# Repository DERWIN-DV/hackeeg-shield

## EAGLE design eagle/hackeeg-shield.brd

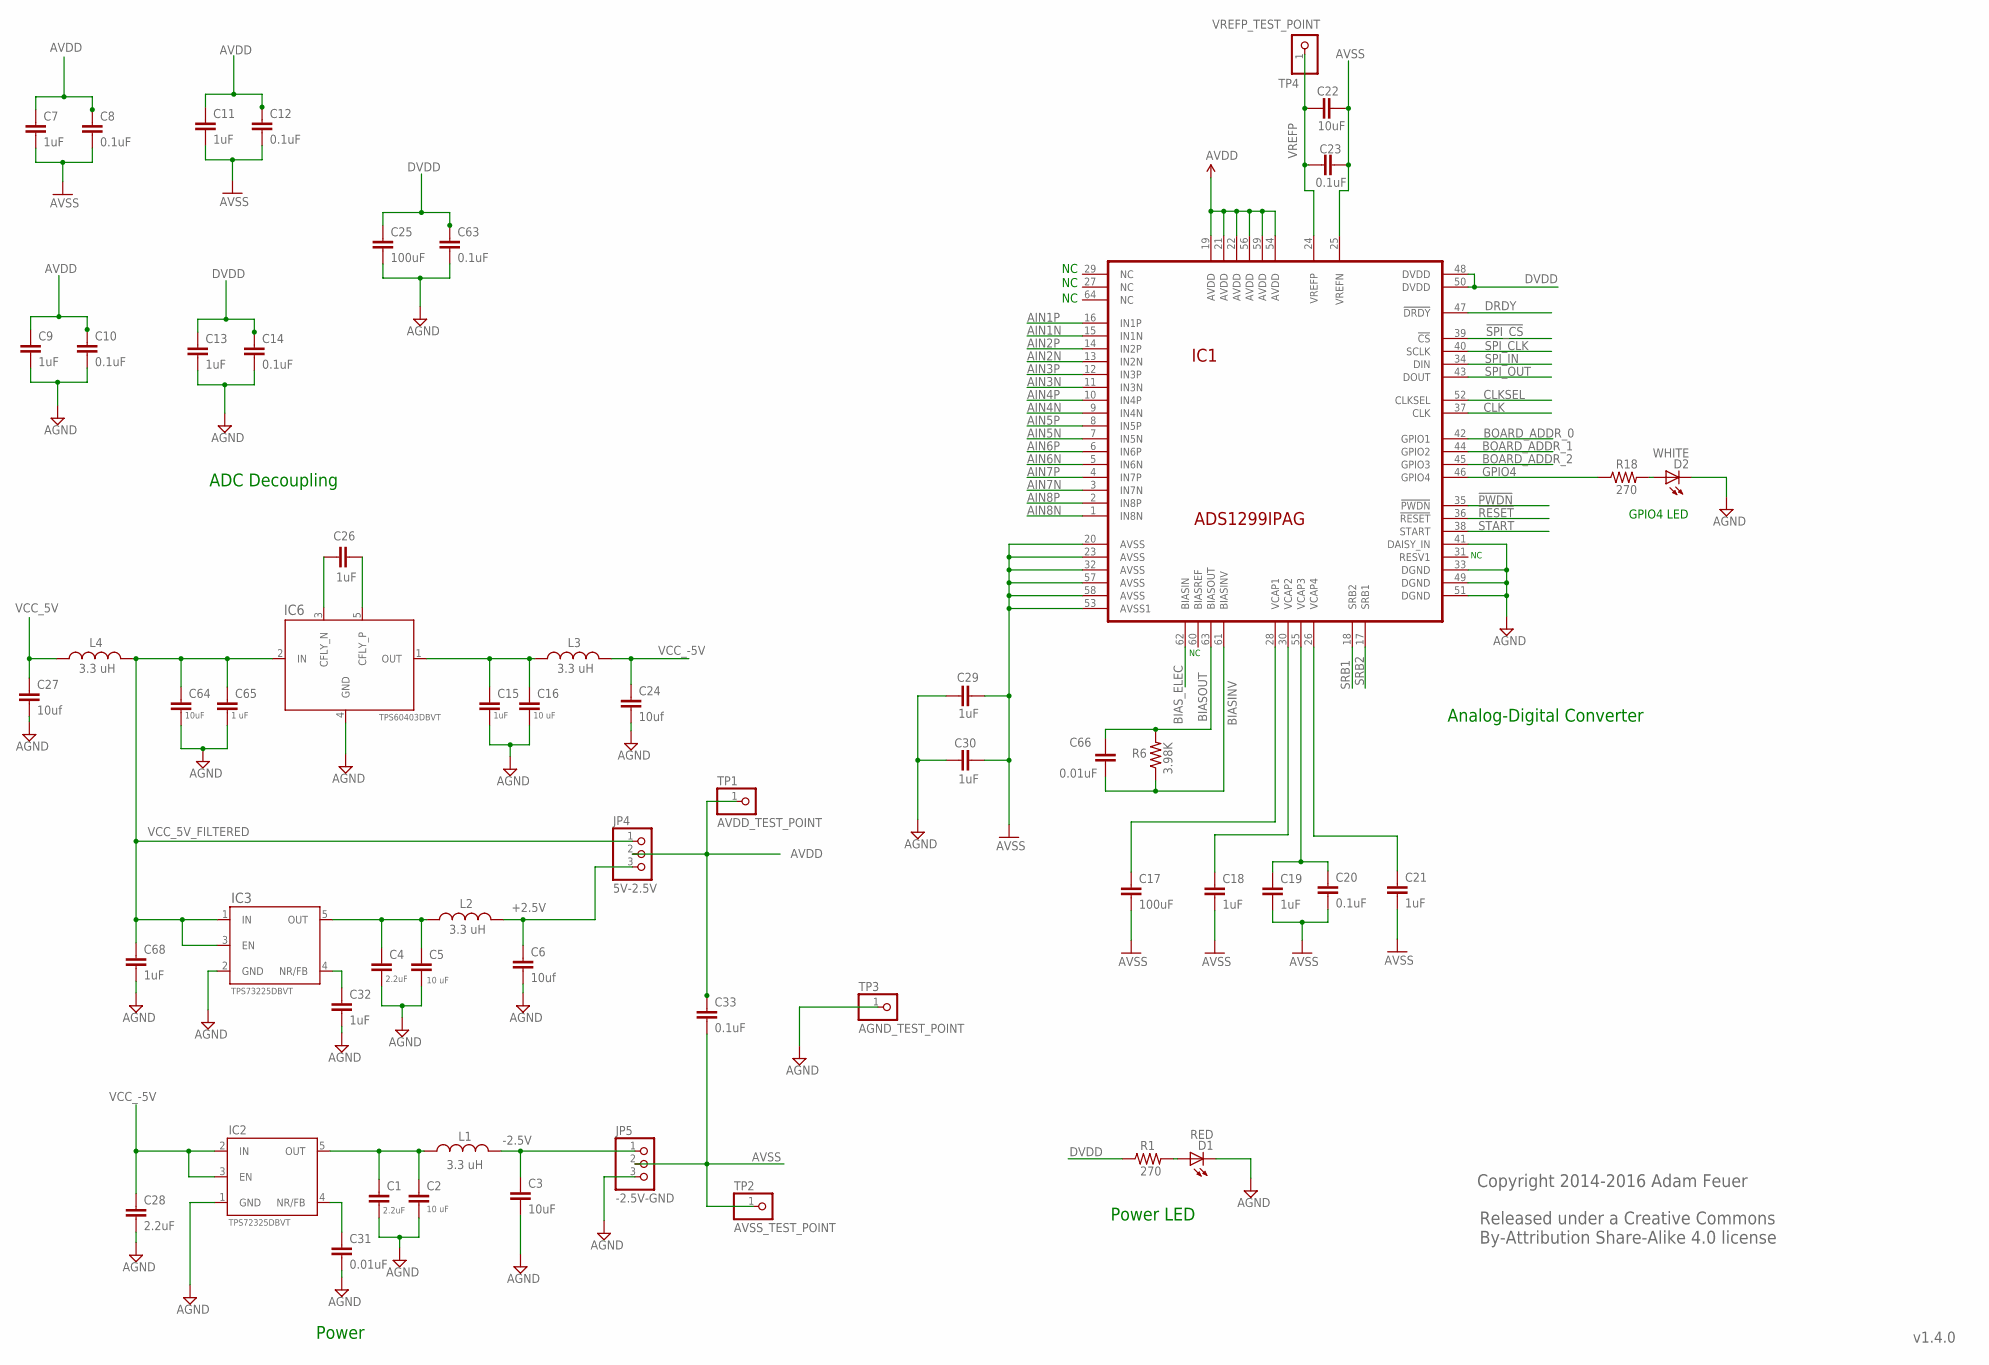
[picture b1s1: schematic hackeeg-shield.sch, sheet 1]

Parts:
C1, C4, C28: 2.2uF; 0603-CAP
C2, C5, C16: 10 uF; 0603-CAP
C3, C22, C64: 10uF; 0603-CAP
C6, C24, C27: 10uf; 0603-CAP
C7, C9, C11, C13, C15, C18, C19, C21, C26, C29, C30, C32, C68: 1uF; 0603-CAP
C8, C10, C12, C14, C20, C23, C33, C63: 0.1uF; 0603-CAP
C17, C25: 100uF; 1210
C31, C66: 0.01uF; 0603-CAP
C65: 1 uF; 0603-CAP
D1: RED; LED-1206
D2: WHITE; LED-1206
IC1: ADS1299IPAG; TQFP64
IC2: TPS72325DBVT; SOT23-5
IC3: TPS73225DBVT; SOT23-5
IC6: TPS60403DBVT; SOT23-5
JP4: 5V-2.5V; 1X03
JP5: -2.5V-GND; 1X03
L1, L2, L3, L4: 3.3 uH; 0805
R1, R18: 270; 0603-RES
R6: 3.98K; 0603-RES
TP1: AVDD_TEST_POINT; 1X01
TP2: AVSS_TEST_POINT; 1X01
TP3: AGND_TEST_POINT; 1X01
TP4: VREFP_TEST_POINT; 1X01

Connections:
!PWDN: IC1.35 (!PWDN); also elsewhere on the board
!RESET: IC1.36 (!RESET); also elsewhere on the board
!SPI_CS: IC1.39 (!CS); also elsewhere on the board
+2.5V: C6.1, JP4.3, L2.2
-2.5V: C3.1, JP5.1, L1.2
AGND: C1.2, C2.2, C3.2, C4.2, C5.2, C6.2, C9.2, C10.2, C13.2, C14.2, C15.2, C16.2, C24.2, C25.2, C27.2, C28.2, C29.1, C30.1, C31.2, C32.2, C63.2, C64.2, C65.2, C68.2, D1.C, D2.C, IC1.33 (DGND), IC1.41 (DAISY_IN), IC1.49 (DGND), IC1.51 (DGND), IC2.1 (GND), IC3.2 (GND), IC6.4 (GND), JP5.3, TP3.1; also elsewhere on the board
AIN1N: IC1.15 (IN1N); also elsewhere on the board
AIN1P: IC1.16 (IN1P); also elsewhere on the board
AIN2N: IC1.13 (IN2N); also elsewhere on the board
AIN2P: IC1.14 (IN2P); also elsewhere on the board
AIN3N: IC1.11 (IN3N); also elsewhere on the board
AIN3P: IC1.12 (IN3P); also elsewhere on the board
AIN4N: IC1.9 (IN4N); also elsewhere on the board
AIN4P: IC1.10 (IN4P); also elsewhere on the board
AIN5N: IC1.7 (IN5N); also elsewhere on the board
AIN5P: IC1.8 (IN5P); also elsewhere on the board
AIN6N: IC1.5 (IN6N); also elsewhere on the board
AIN6P: IC1.6 (IN6P); also elsewhere on the board
AIN7N: IC1.3 (IN7N); also elsewhere on the board
AIN7P: IC1.4 (IN7P); also elsewhere on the board
AIN8N: IC1.1 (IN8N); also elsewhere on the board
AIN8P: IC1.2 (IN8P); also elsewhere on the board
AVDD: C7.1, C8.1, C9.1, C10.1, C11.1, C12.1, C33.1, IC1.19 (AVDD), IC1.21 (AVDD), IC1.22 (AVDD), IC1.54 (AVDD), IC1.56 (AVDD), IC1.59 (AVDD), JP4.2, TP1.1; also elsewhere on the board
AVSS: C7.2, C8.2, C11.2, C12.2, C17.2, C18.2, C19.2, C20.2, C21.2, C22.2, C23.2, C29.2, C30.2, C33.2, IC1.20 (AVSS), IC1.23 (AVSS), IC1.25 (VREFN), IC1.32 (AVSS), IC1.53 (AVSS1), IC1.57 (AVSS), IC1.58 (AVSS), JP5.2, TP2.1; also elsewhere on the board
BIASINV: C66.2, IC1.61 (BIASINV), R6.1; also elsewhere on the board
BIASOUT: C66.1, IC1.63 (BIASOUT), R6.2; also elsewhere on the board
BIAS_ELEC: IC1.62 (BIASIN); also elsewhere on the board
BOARD_ADDR_0: IC1.42 (GPIO1); also elsewhere on the board
BOARD_ADDR_1: IC1.44 (GPIO2); also elsewhere on the board
BOARD_ADDR_2: IC1.45 (GPIO3); also elsewhere on the board
CLK: IC1.37 (CLK); also elsewhere on the board
CLKSEL: IC1.52 (CLKSEL); also elsewhere on the board
DRDY: IC1.47 (!DRDY); also elsewhere on the board
DVDD: C13.1, C14.1, C25.1, C63.1, IC1.48 (DVDD), IC1.50 (DVDD), R1.1; also elsewhere on the board
GPIO4: IC1.46 (GPIO4), R18.1
unnamed: C4.1, C5.1, IC3.5 (OUT), L2.1
unnamed: C1.1, C2.1, IC2.5 (OUT), L1.1
unnamed: C17.1, IC1.28 (VCAP1)
unnamed: C18.1, IC1.30 (VCAP2)
unnamed: C19.1, C20.1, IC1.55 (VCAP3)
unnamed: C15.1, C16.1, IC6.1 (OUT), L3.1
unnamed: C21.1, IC1.26 (VCAP4)
unnamed: C26.2, IC6.5 (CFLY_P)
unnamed: C26.1, IC6.3 (CFLY_N)
unnamed: C32.1, IC3.4 (NR/FB)
unnamed: C31.1, IC2.4 (NR/FB)
unnamed: D2.A, R18.2
unnamed: D1.A, R1.2
SPI_CLK: IC1.40 (SCLK); also elsewhere on the board
SPI_IN: IC1.34 (DIN); also elsewhere on the board
SPI_OUT: IC1.43 (DOUT); also elsewhere on the board
SRB1: IC1.18 (SRB2); also elsewhere on the board
SRB2: IC1.17 (SRB1); also elsewhere on the board
START: IC1.38 (START); also elsewhere on the board
VCC_5V: C27.1, L4.1; also elsewhere on the board
VCC_5V_FILTERED: C64.1, C65.1, C68.1, IC3.1 (IN), IC3.3 (EN), IC6.2 (IN), JP4.1, L4.2
VCC_-5V: C24.1, C28.1, IC2.2 (IN), IC2.3 (EN), L3.2
VREFP: C22.1, C23.1, IC1.24 (VREFP), TP4.1

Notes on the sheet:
Released under a Creative Commons By-Attribution Share-Alike 4.0 license
Copyright 2014-2016 Adam Feuer
v1.4.0
ADC Decoupling
Power
Analog-Digital Converter
GPIO4 LED
Power LED

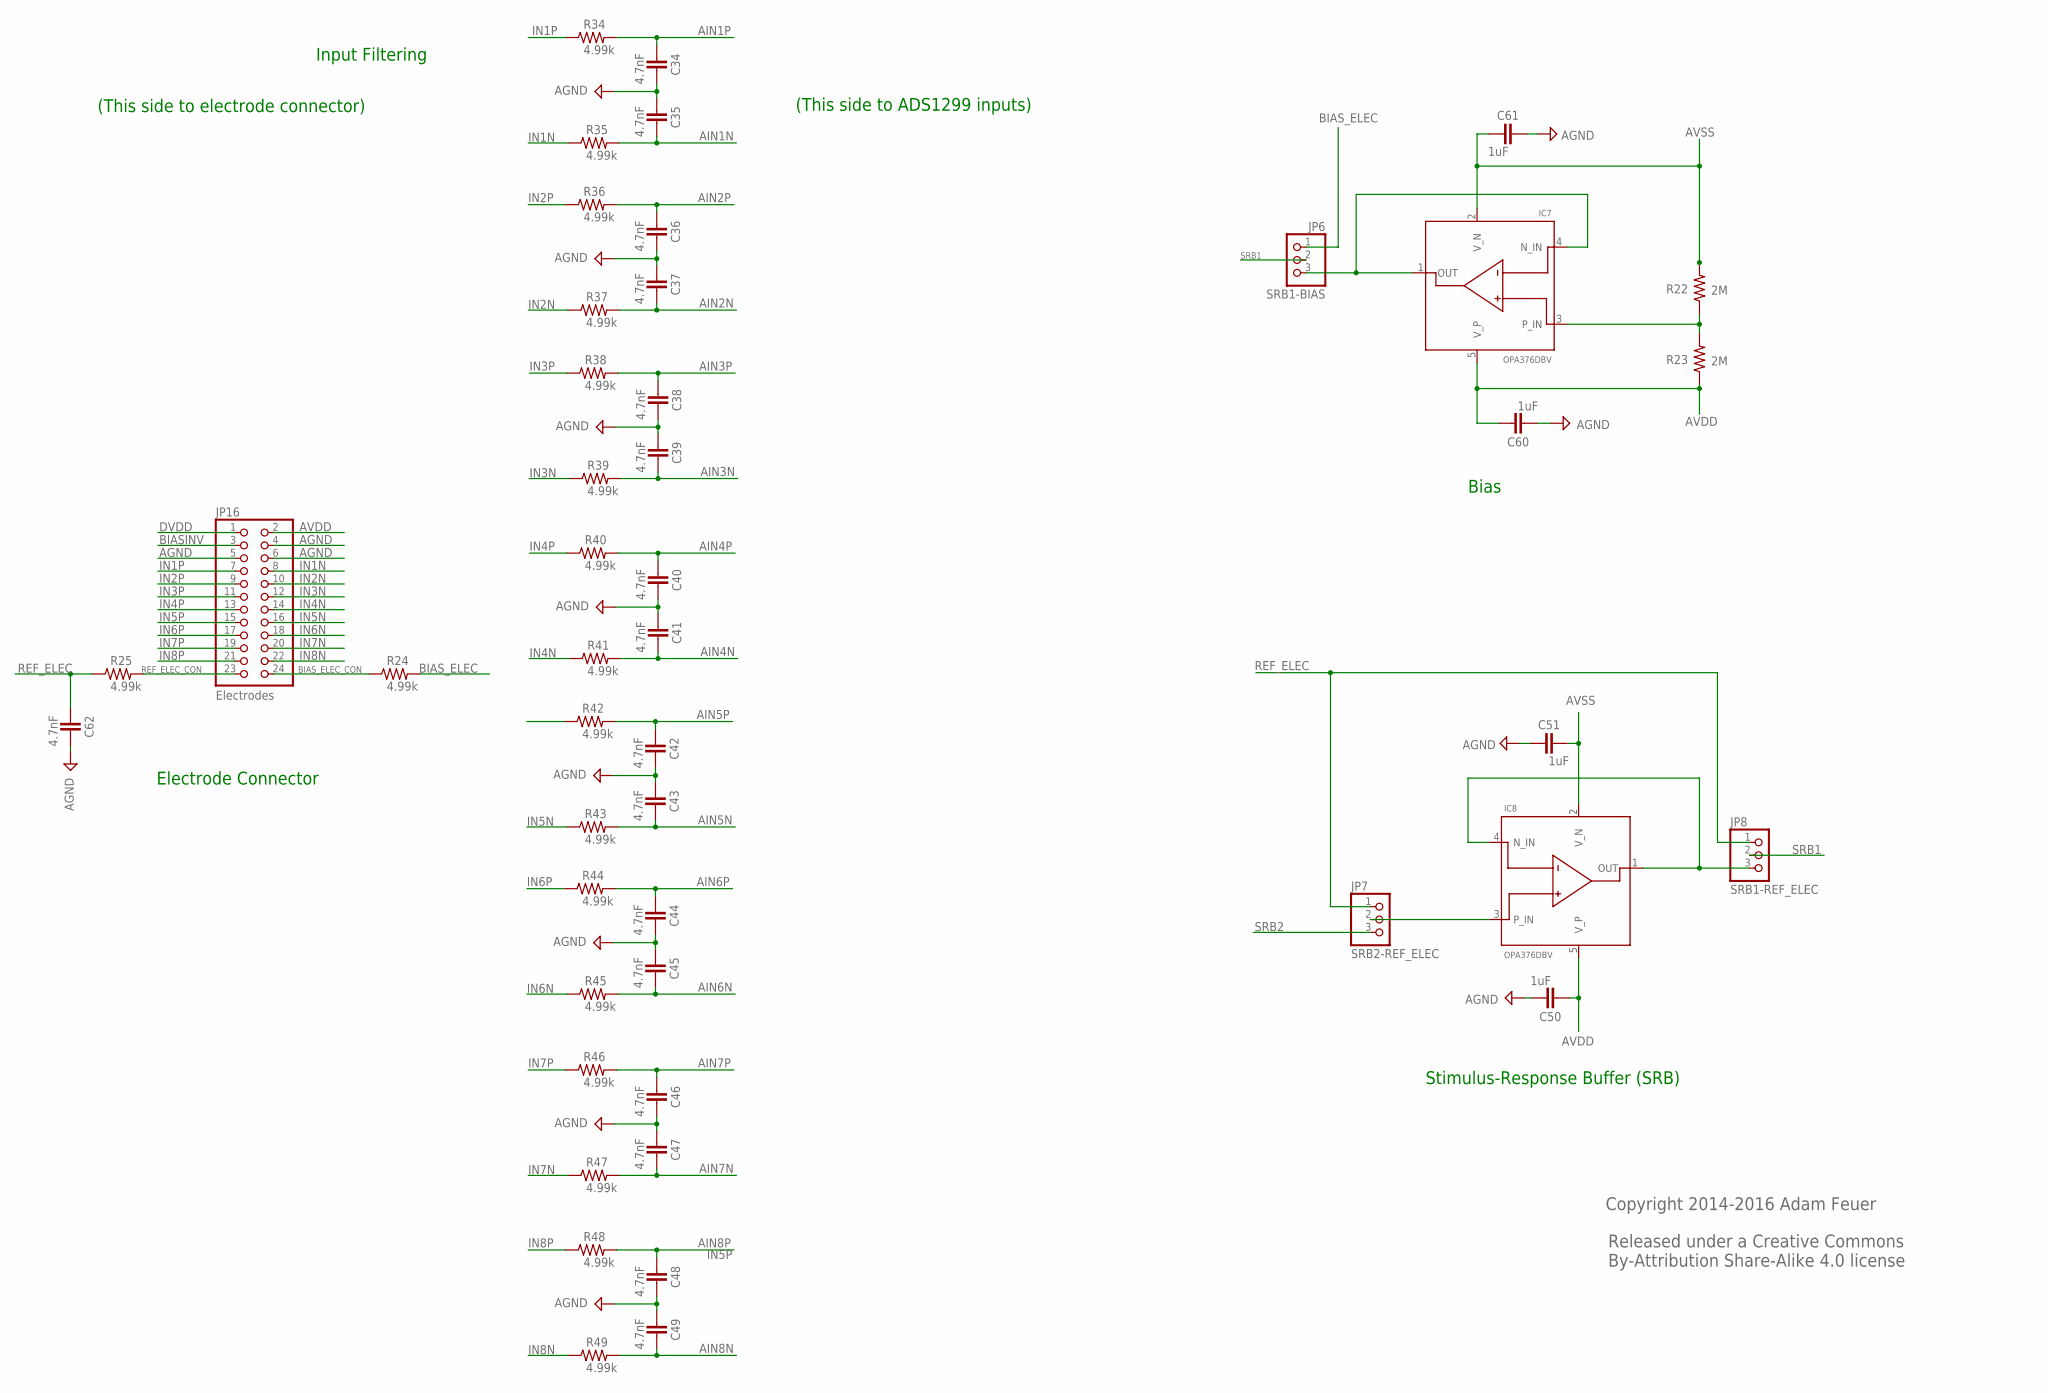
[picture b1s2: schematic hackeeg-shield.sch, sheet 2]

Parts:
C34, C35, C36, C37, C38, C39, C40, C41, C42, C43, C44, C45, C46, C47, C48, C49, C62: 4.7nF; 0603-CAP
C50, C51, C60, C61: 1uF; 0603-CAP
IC7, IC8: OPA376DBV; SOT23-5
JP6: SRB1-BIAS; 1X03
JP7: SRB2-REF_ELEC; 1X03
JP8: SRB1-REF_ELEC; 1X03
JP16: Electrodes; 2X12
R22, R23: 2M; 0603-RES
R24, R25, R34, R35, R36, R37, R38, R39, R40, R41, R42, R43, R44, R45, R46, R47, R48, R49: 4.99k; 0603-RES

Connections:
AGND: C34.2, C35.1, C36.2, C37.1, C38.2, C39.1, C40.2, C41.1, C42.2, C43.1, C44.2, C45.1, C46.2, C47.1, C48.2, C49.1, C50.2, C51.1, C60.2, C61.1, C62.2, JP16.4, JP16.5, JP16.6; also elsewhere on the board
AIN1N: C35.2, R35.2; also elsewhere on the board
AIN1P: C34.1, R34.2; also elsewhere on the board
AIN2N: C37.2, R37.2; also elsewhere on the board
AIN2P: C36.1, R36.2; also elsewhere on the board
AIN3N: C39.2, R39.2; also elsewhere on the board
AIN3P: C38.1, R38.2; also elsewhere on the board
AIN4N: C41.2, R41.2; also elsewhere on the board
AIN4P: C40.1, R40.2; also elsewhere on the board
AIN5N: C43.2, R43.2; also elsewhere on the board
AIN5P: C42.1, R42.2; also elsewhere on the board
AIN6N: C45.2, R45.2; also elsewhere on the board
AIN6P: C44.1, R44.2; also elsewhere on the board
AIN7N: C47.2, R47.2; also elsewhere on the board
AIN7P: C46.1, R46.2; also elsewhere on the board
AIN8N: C49.2, R49.2; also elsewhere on the board
AIN8P: C48.1, R48.2; also elsewhere on the board
AVDD: C50.1, C60.1, IC7.5 (V_P), IC8.5 (V_P), JP16.2, R23.1; also elsewhere on the board
AVSS: C51.2, C61.2, IC7.2 (V_N), IC8.2 (V_N), R22.2; also elsewhere on the board
BIASINV: JP16.3; also elsewhere on the board
BIAS_ELEC: JP6.1, R24.2; also elsewhere on the board
BIAS_ELEC_CON: JP16.24, R24.1
DVDD: JP16.1; also elsewhere on the board
IN1N: JP16.8, R35.1
IN1P: JP16.7, R34.1
IN2N: JP16.10, R37.1
IN2P: JP16.9, R36.1
IN3N: JP16.12, R39.1
IN3P: JP16.11, R38.1
IN4N: JP16.14, R41.1
IN4P: JP16.13, R40.1
IN5N: JP16.16, R43.1
IN5P: JP16.15, R42.1
IN6N: JP16.18, R45.1
IN6P: JP16.17, R44.1
IN7N: JP16.20, R47.1
IN7P: JP16.19, R46.1
IN8N: JP16.22, R49.1
IN8P: JP16.21, R48.1
unnamed: IC7.3 (P_IN), R22.1, R23.2
unnamed: IC8.3 (P_IN), JP7.2
unnamed: IC8.1 (OUT), IC8.4 (N_IN), JP8.3
unnamed: IC7.1 (OUT), IC7.4 (N_IN), JP6.3
REF_ELEC: C62.1, JP7.1, JP8.1, R25.1
REF_ELEC_CON: JP16.23, R25.2
SRB1: JP6.2, JP8.2; also elsewhere on the board
SRB2: JP7.3; also elsewhere on the board

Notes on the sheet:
Electrode Connector
Stimulus-Response Buffer (SRB)
Bias
Released under a Creative Commons By-Attribution Share-Alike 4.0 license
Copyright 2014-2016 Adam Feuer
Input Filtering
(This side to ADS1299 inputs)
(This side to electrode connector)

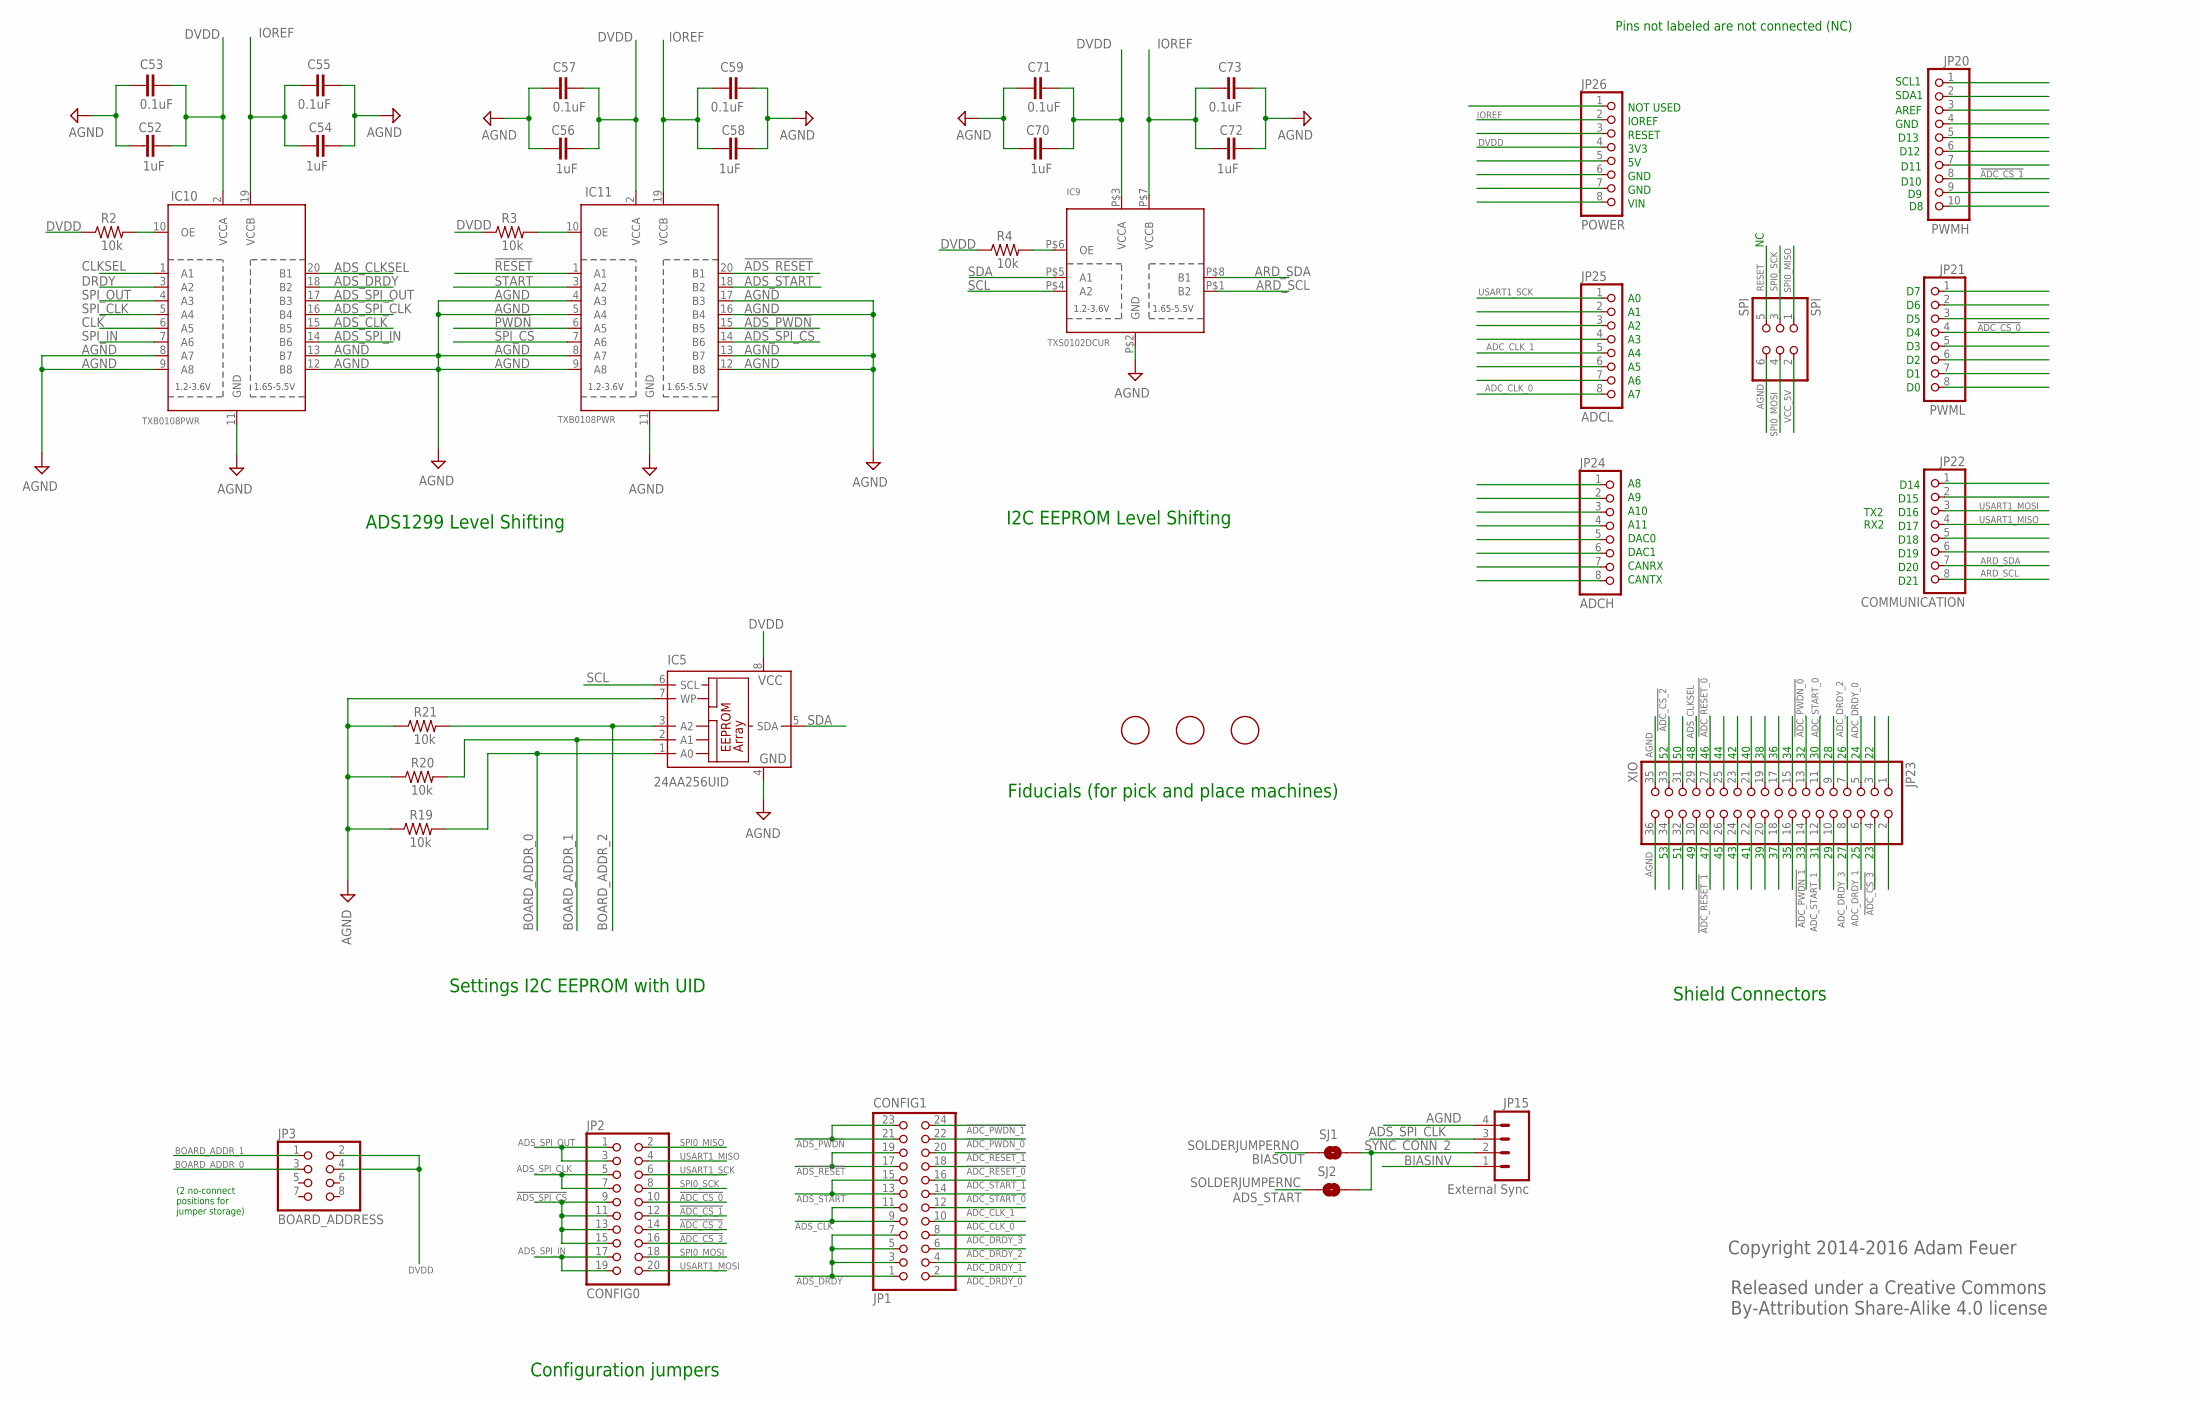
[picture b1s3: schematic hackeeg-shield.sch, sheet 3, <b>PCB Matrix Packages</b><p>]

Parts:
C52, C54, C56, C58, C70, C72: 1uF; 0603-CAP
C53, C55, C57, C59, C71, C73: 0.1uF; 0603-CAP
IC5: 24AA256UID; SO-08
IC9: TXS0102DCUR; VFSOP-8
IC10, IC11: TXB0108PWR; TSSOP20
JP1: CONFIG1; 2X12
JP2: CONFIG0; 2X10
JP3: BOARD_ADDRESS; 2X04
JP15: External Sync; JST-4-PTH
JP20: PWMH; 1X10
JP21: PWML; 1X08
JP22: COMMUNICATION; 1X08
JP23: XIO; 2X18
JP24: ADCH; 1X08
JP25: ADCL; 1X08
JP26: POWER; 1X08
R2, R3, R4, R19, R20, R21: 10k; 0603-RES
SJ1: SOLDERJUMPERNO; SJ_2S-NO
SJ2: SOLDERJUMPERNC; SJ_2S
SPI: SPI; 2X03
U$2, U$5, U$6: FIDUCIAL; FIDUCIAL_1MM

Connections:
!ADC_CS_0: JP2.10, JP21.4
!ADC_CS_1: JP2.12, JP20.8
!ADC_CS_2: JP2.14, JP23.33
!ADC_CS_3: JP2.16, JP23.4
!ADC_PWDN_0: JP1.22, JP23.13
!ADC_PWDN_1: JP1.24, JP23.14
!ADC_RESET_0: JP1.18, JP23.27
!ADC_RESET_1: JP1.20, JP23.28
!ADS_PWDN: IC11.15 (B5), JP1.21, JP1.23
!ADS_RESET: IC11.20 (B1), JP1.17, JP1.19
!ADS_SPI_CS: IC11.14 (B6), JP2.9, JP2.11, JP2.13, JP2.15
!PWDN: IC11.6 (A5); also elsewhere on the board
!RESET: IC11.1 (A1); also elsewhere on the board
!SPI_CS: IC11.7 (A6); also elsewhere on the board
ADC_CLK_0: JP1.10, JP25.8
ADC_CLK_1: JP1.12, JP25.5
ADC_DRDY_0: JP1.2, JP23.5
ADC_DRDY_1: JP1.4, JP23.6
ADC_DRDY_2: JP1.6, JP23.7
ADC_DRDY_3: JP1.8, JP23.8
ADC_START_0: JP1.14, JP23.11
ADC_START_1: JP1.16, JP23.12
ADS_CLK: IC10.15 (B5), JP1.9, JP1.11
ADS_CLKSEL: IC10.20 (B1), JP23.29
ADS_DRDY: IC10.18 (B2), JP1.1, JP1.3, JP1.5, JP1.7
ADS_SPI_CLK: IC10.16 (B4), JP2.5, JP2.7, JP15.3
ADS_SPI_IN: IC10.14 (B6), JP2.17, JP2.19
ADS_SPI_OUT: IC10.17 (B3), JP2.1, JP2.3
ADS_START: IC11.18 (B2), JP1.13, JP1.15, SJ2.1
AGND: C52.1, C53.1, C54.1, C55.1, C56.1, C57.1, C58.1, C59.1, C70.1, C71.1, C72.1, C73.1, IC5.4 (GND), IC5.7 (WP), IC9.P$2 (GND), IC10.8 (A7), IC10.9 (A8), IC10.11 (GND), IC10.12 (B8), IC10.13 (B7), IC11.4 (A3), IC11.5 (A4), IC11.8 (A7), IC11.9 (A8), IC11.11 (GND), IC11.12 (B8), IC11.13 (B7), IC11.16 (B4), IC11.17 (B3), JP15.4, JP23.35, JP23.36, R19.1, R20.1, R21.1, SPI.6; also elsewhere on the board
ARD_SCL: IC9.P$1 (B2), JP22.8
ARD_SDA: IC9.P$8 (B1), JP22.7
BIASINV: JP15.1; also elsewhere on the board
BIASOUT: SJ1.1; also elsewhere on the board
BOARD_ADDR_0: IC5.1 (A0), JP3.3, R19.2; also elsewhere on the board
BOARD_ADDR_1: IC5.2 (A1), JP3.1, R20.2; also elsewhere on the board
BOARD_ADDR_2: IC5.3 (A2), R21.2; also elsewhere on the board
CLK: IC10.6 (A5); also elsewhere on the board
CLKSEL: IC10.1 (A1); also elsewhere on the board
DRDY: IC10.3 (A2); also elsewhere on the board
DVDD: C52.2, C53.2, C56.2, C57.2, C70.2, C71.2, IC5.8 (VCC), IC9.P$3 (VCCA), IC10.2 (VCCA), IC11.2 (VCCA), JP3.2, JP3.4, JP26.4, R2.1, R3.1, R4.1; also elsewhere on the board
IOREF: C54.2, C55.2, C58.2, C59.2, C72.2, C73.2, IC9.P$7 (VCCB), IC10.19 (VCCB), IC11.19 (VCCB), JP26.2
unnamed: IC9.P$6 (OE), R4.2
unnamed: IC10.10 (OE), R2.2
unnamed: IC11.10 (OE), R3.2
RESET: SPI.5
SCL: IC5.6 (SCL), IC9.P$4 (A2)
SDA: IC5.5 (SDA), IC9.P$5 (A1)
SPI0_MISO: JP2.2, SPI.1
SPI0_MOSI: JP2.18, SPI.4
SPI0_SCK: JP2.8, SPI.3
SPI_CLK: IC10.5 (A4); also elsewhere on the board
SPI_IN: IC10.7 (A6); also elsewhere on the board
SPI_OUT: IC10.4 (A3); also elsewhere on the board
START: IC11.3 (A2); also elsewhere on the board
SYNC_CONN_2: JP15.2, SJ1.2, SJ2.2
USART1_MISO: JP2.4, JP22.4
USART1_MOSI: JP2.20, JP22.3
USART1_SCK: JP2.6, JP25.1
VCC_5V: SPI.2; also elsewhere on the board

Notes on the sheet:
Configuration jumpers
ADS1299 Level Shifting
Settings I2C EEPROM with UID
(2 no-connect positions for jumper storage)
Released under a Creative Commons By-Attribution Share-Alike 4.0 license
Copyright 2014-2016 Adam Feuer
Shield Connectors
SCL1
SDA1
AREF
GND
D14
D15
D16
D17
D18
D19
D20
D21
A10
A11
DAC0
DAC1
CANRX
CANTX
NOT USED
IOREF
RESET
3V3
VIN
Fiducials (for pick and place machines)
TX2
RX2
I2C EEPROM Level Shifting
Pins not labeled are not connected (NC)
D13
D12
D11
D10

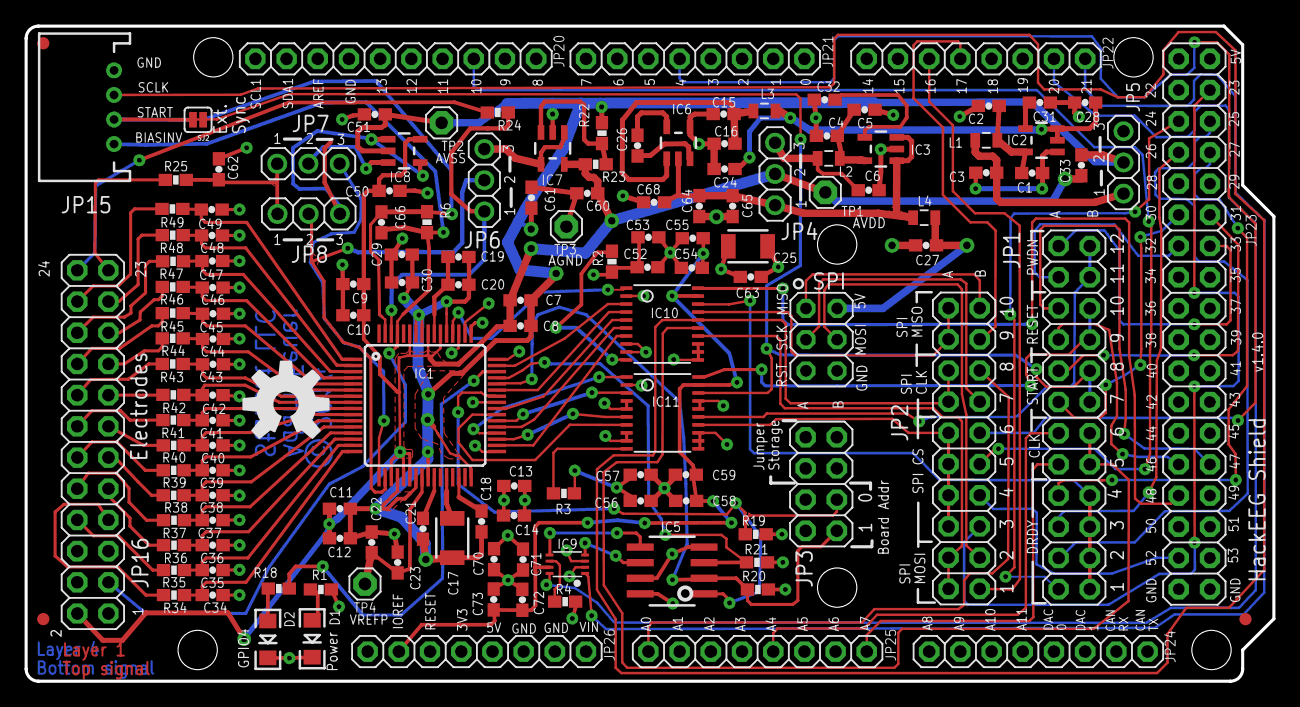
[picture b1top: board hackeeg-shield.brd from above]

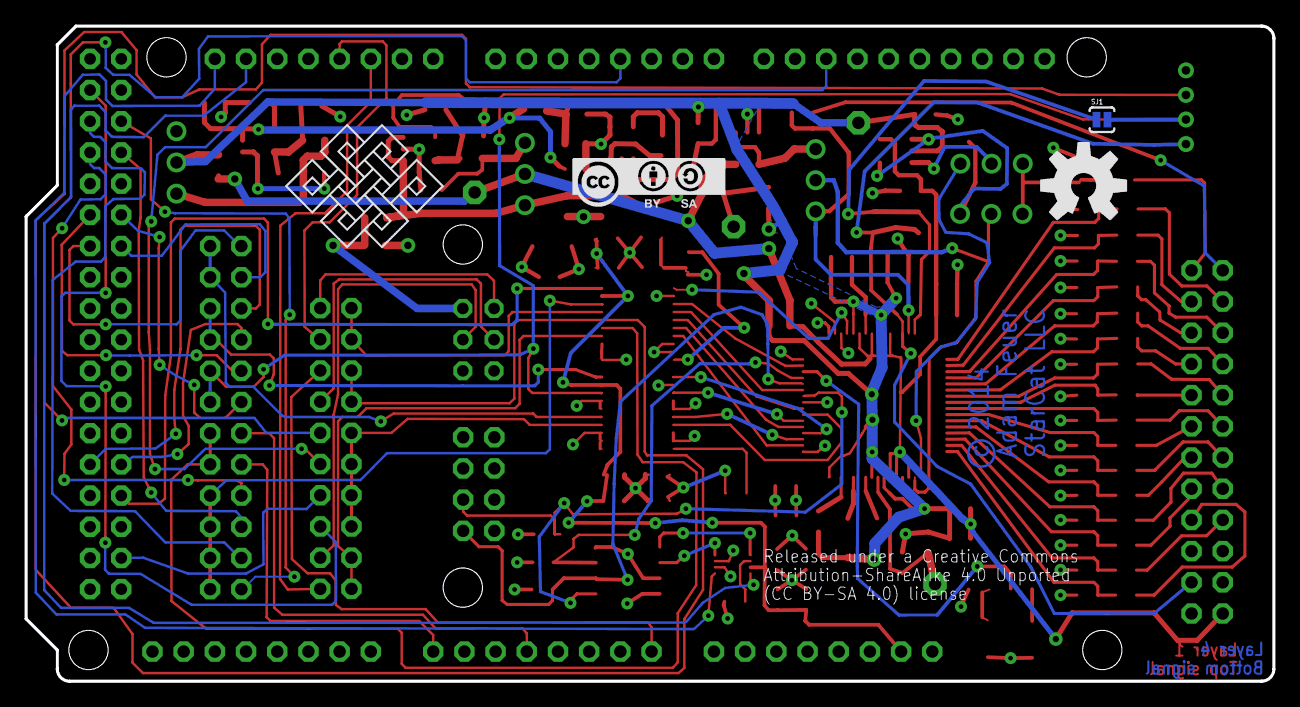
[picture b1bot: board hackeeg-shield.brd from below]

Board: 4 copper layers, 101.6 x 53.3 mm, 147 parts (4 on the bottom side), 122 nets.

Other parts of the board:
U$1, U$4: OSHW-LOGO-L
U$3: CC-BY-SA
U$7: ENDLESSKNOT-MEDIUM

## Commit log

2016-09-01 add option to put biasout on ext sync connector
    - probably won't use this option, saving it just in case

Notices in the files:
eagle/hackeeg-shield.brd:
Attribution-ShareAlike 4.0 Unported
(CC BY-SA 4.0) license
parts and their libraries:
SparkFun-Passives: Licensing: CC v3.0 Share-Alike You are welcome to use this library for commercial purposes.
